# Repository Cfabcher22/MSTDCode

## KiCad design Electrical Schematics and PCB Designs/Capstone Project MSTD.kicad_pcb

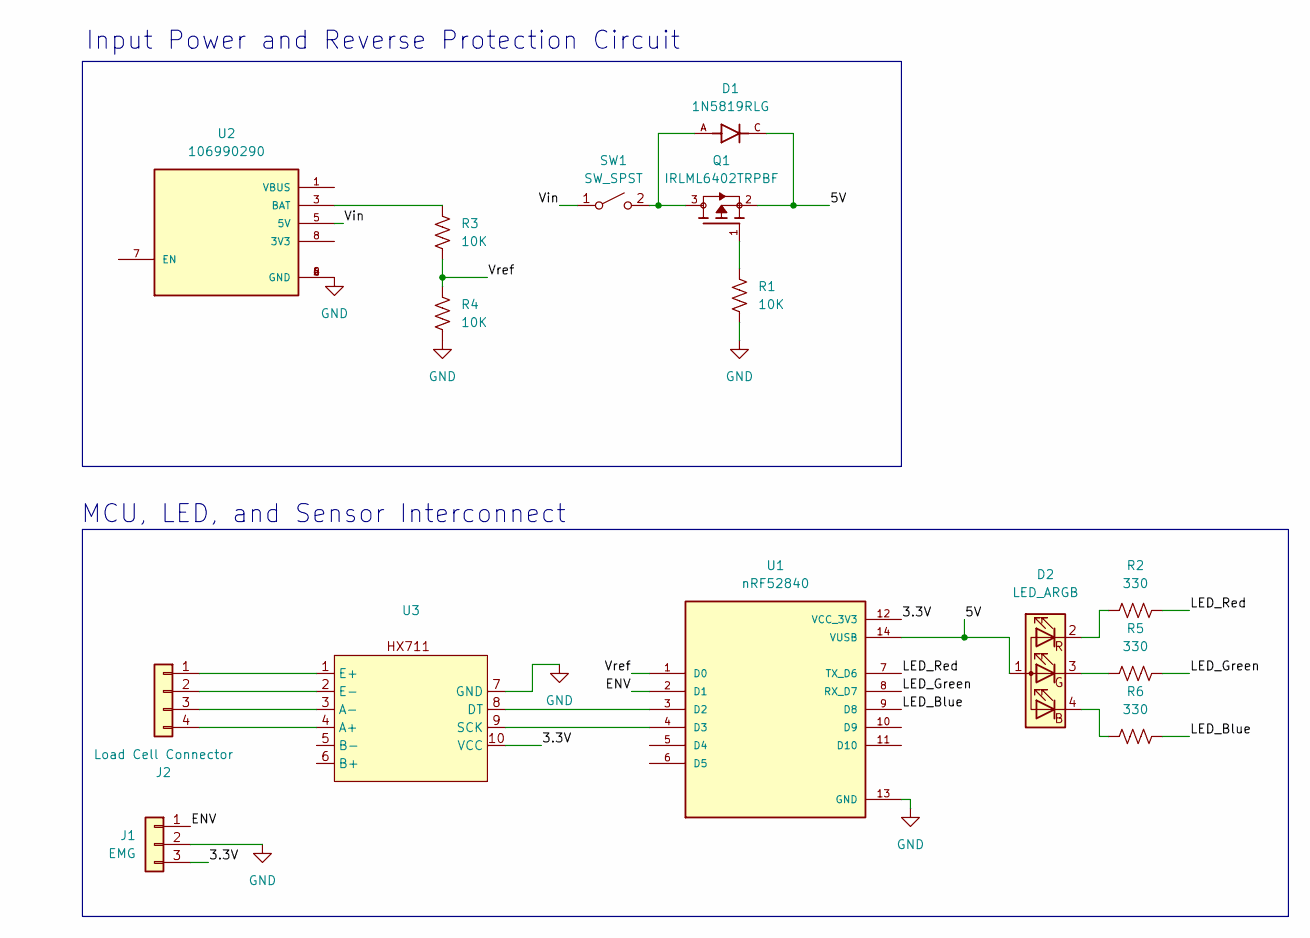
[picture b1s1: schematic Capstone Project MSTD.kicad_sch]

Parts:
D1: 1N5819RLG; DIOAD1036W78L470D235; PARTREV P2104
D2: LED_ARGB; PinHeader_1x04_P2.54mm_Vertical
J1: EMG; PinHeader_1x03_P2.54mm_Vertical
J2: Load Cell Connector; PinHeader_1x04_P2.54mm_Vertical
Q1: IRLML6402TRPBF; SOT95P237X112-3N; PARTREV N/A
R1, R3, R4: 10K; R_0805_2012Metric
R2, R5, R6: 330; R_0805_2012Metric
SW1: SW_SPST; PinHeader_1x02_P2.54mm_Vertical
U1: nRF52840; MODULE_113991054; PARTREV 23/05/2022
U2: 106990290; MODULE_106990290; PARTREV NA; DigiKey_Part_Number 1597-106990290-ND
U3: Untitled

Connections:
/3.3V: J1.3, U1.12 (VCC_3V3), U3.10 (VCC)
/5V: D1.C, D2.1 (A), Q1.2, U1.14 (VUSB)
/ENV: J1.1, U1.2 (D1)
/LED_Blue: R6.2, U1.9 (D8)
/LED_Green: R5.1, U1.8 (RX_D7)
/LED_Red: R2.2, U1.7 (TX_D6)
/Vin: SW1.1 (A), U2.5 (5V)
/Vref: R3.2, R4.1, U1.1 (D0)
GND: J1.2, R1.2, R4.2, U1.13 (GND), U2.2 (GND), U2.4 (GND), U2.6 (GND), U3.7 (GND)
unnamed: D2.4 (BK), R6.1
unnamed: D2.3 (GK), R5.2
unnamed: D2.2 (RK), R2.1
unnamed: J2.1, U3.1 (E+)
unnamed: J2.2, U3.2 (E-)
unnamed: J2.3, U3.3 (A-)
unnamed: J2.4, U3.4 (A+)
unnamed: Q1.1, R1.1
unnamed: D1.A, Q1.3, SW1.2 (B)
unnamed: U1.3 (D2), U3.8 (DT)
unnamed: U1.4 (D3), U3.9 (SCK)
unnamed: R3.1, U2.3 (BAT)

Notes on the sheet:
MCU, LED, and Sensor Interconnect
Input Power and Reverse Protection Circuit

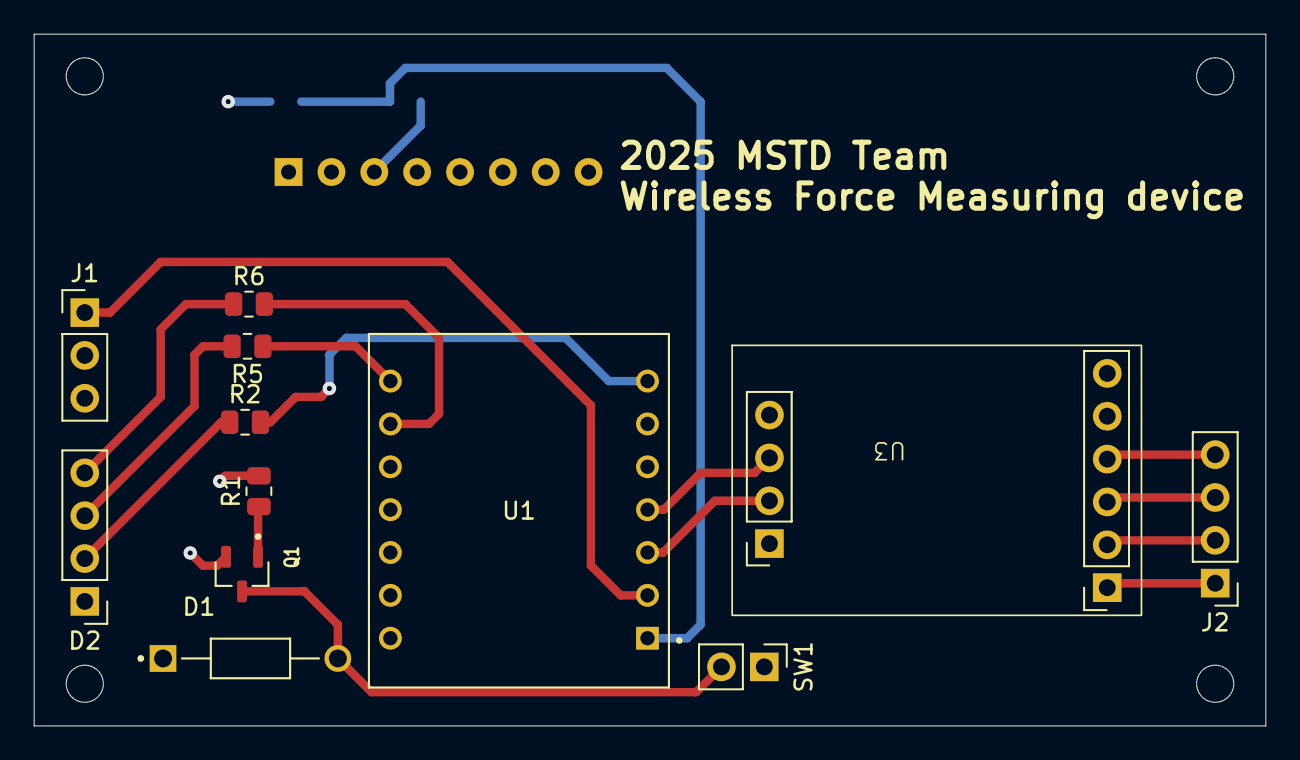
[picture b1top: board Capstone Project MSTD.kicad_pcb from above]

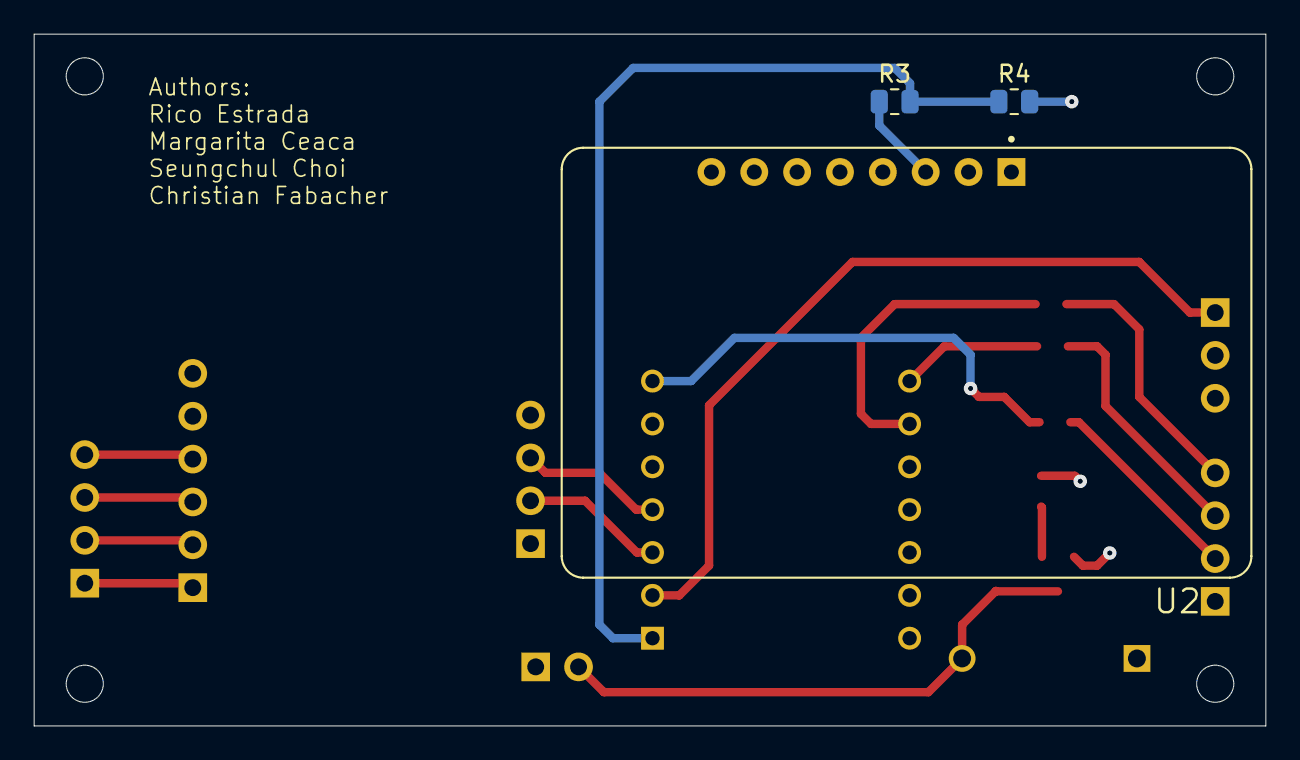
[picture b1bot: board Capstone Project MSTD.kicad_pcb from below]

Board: 4 copper layers, 73.0 x 41.0 mm, 15 parts (3 on the bottom side), 21 nets.

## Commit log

2025-05-01 add an example txt
2025-05-01 saved a file change to only my branch
2025-06-05 updated giga code
2025-06-07 EMG sensor code added
2025-06-13 Added GUI Codes
2025-06-13 Updated Force Sensor Code
2025-06-27 Added wired Arudino to Workstation code and EMG test code
2025-07-07 added External LED test code
2025-07-09 added GIGA to GIGA BLE communication code
2025-07-17 Revised Giga code to support receive force data with nrf
2025-07-17 Added Final and Completed prototype codes
2025-07-31 Created testing code for BLE range testing
2025-08-06 created load cell testing code
2025-08-07 updated load cell cal test
2025-08-07 creaed a final complied test code
2025-08-07 added nrf complied test code
2025-08-10 Updated battery LED code
2025-08-15 latest test code for giga and nrf
2025-08-15 zipped complied codes
2025-08-15 edited main and receiver giga to communicate via ble
2025-08-15 latest rev code
2025-08-15 updated receiver giga code
2025-08-15 new code
2025-08-15 new receiver code
2025-08-15 added Giga 1 cage code
2025-08-22 Ricos resent codes
2025-08-22 FINAL NRF working code
2025-08-25 Uploaded final codes and PCB files
2025-08-25 Uploaded electrical schematic
